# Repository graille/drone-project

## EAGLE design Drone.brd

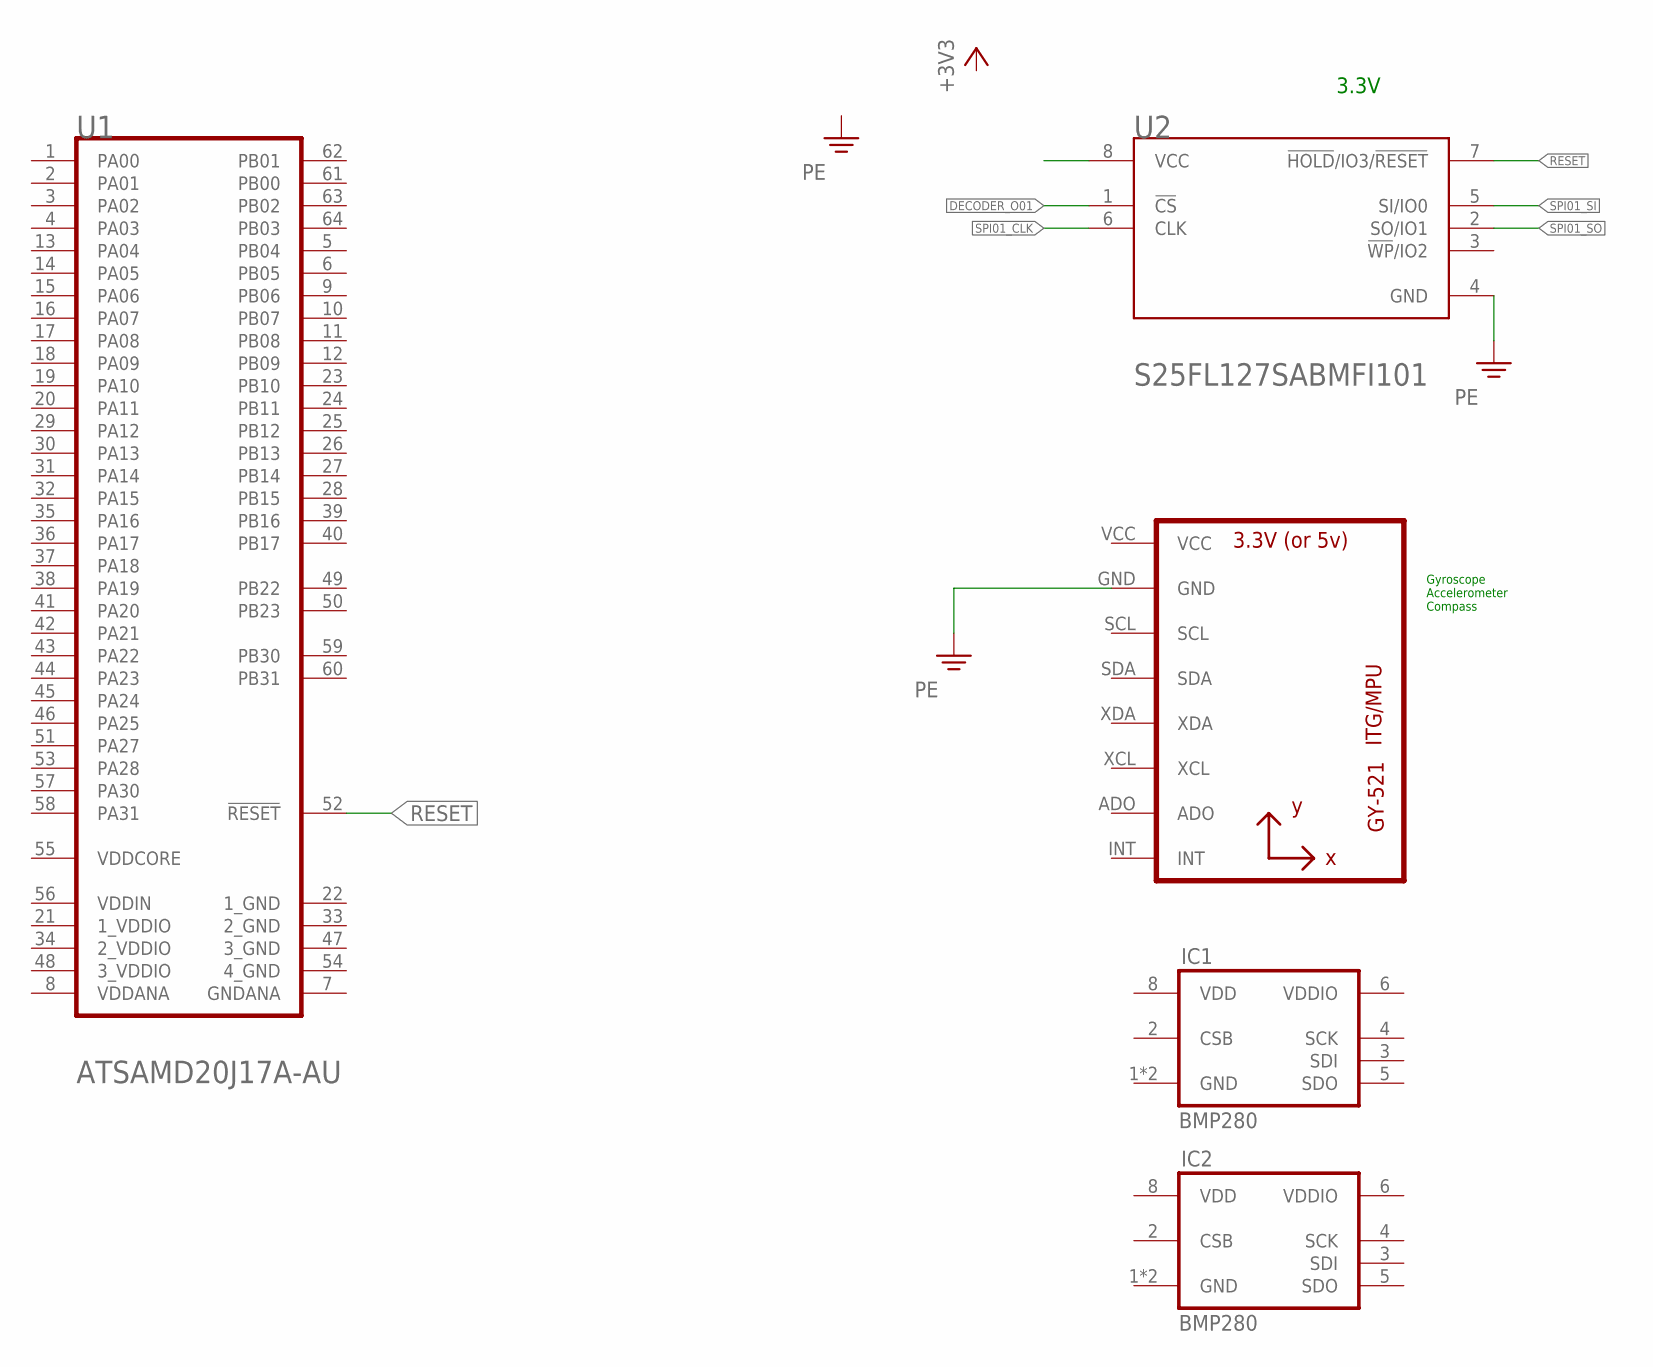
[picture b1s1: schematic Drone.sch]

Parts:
IC1, IC2: BMP280
U1: ATMEL_ATSAMD20J17A-AUATMEL_ATSAMD20J17A-AU_0_0; ATMEL_ATSAMD20J17A-AU_0
U2: CYPRESS_S25FL127SABMFI101CYPRESS_S25FL127SABMFI10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; CYPRESS_S25FL127SABMFI101_0
U3: GY-521MPU6050; GY-521

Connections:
1_GND: U1.22 (1_GND)
1_VDDIO: U1.21 (1_VDDIO)
2_GND: U1.33 (2_GND)
2_VDDIO: U1.34 (2_VDDIO)
3_GND: U1.47 (3_GND)
3_VDDIO: U1.48 (3_VDDIO)
4_GND: U1.54 (4_GND)
DECODER_O01: U2.1 (!CS!)
GND: IC1.1 (GND), IC1.7 (GND), IC2.1 (GND), IC2.7 (GND)
GNDANA: U1.7 (GNDANA)
PE: U2.4 (GND)
RESET: U1.52 (!RESET!), U2.7 (!HOLD!/IO3/!RESET!)
SPI01_CLK: U2.6 (CLK)
SPI01_SI: U2.5 (SI/IO0)
SPI01_SO: U2.2 (SO/IO1)
VDD: IC1.8 (VDD), IC2.8 (VDD)
VDDANA: U1.8 (VDDANA)
VDDCORE: U1.55 (VDDCORE)
VDDIN: U1.56 (VDDIN)
VDDIO: IC1.6 (VDDIO), IC2.6 (VDDIO)

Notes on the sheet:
3.3V
Gyroscope Accelerometer Compass

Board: 2 copper layers, 5 parts (0 on the bottom side), 4 nets, no tracks yet.

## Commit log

2019-03-04 Add project files
